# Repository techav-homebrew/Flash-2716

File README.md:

# Flash-2716

This is an adapter for using a 39F010 similar PLCC-32 flash in place of a 2716 or 2732 EPROM. Includes footprint & jumper to use original EPROM as well as an additional disconnected footprint for storing the original EPROM out of circuit.

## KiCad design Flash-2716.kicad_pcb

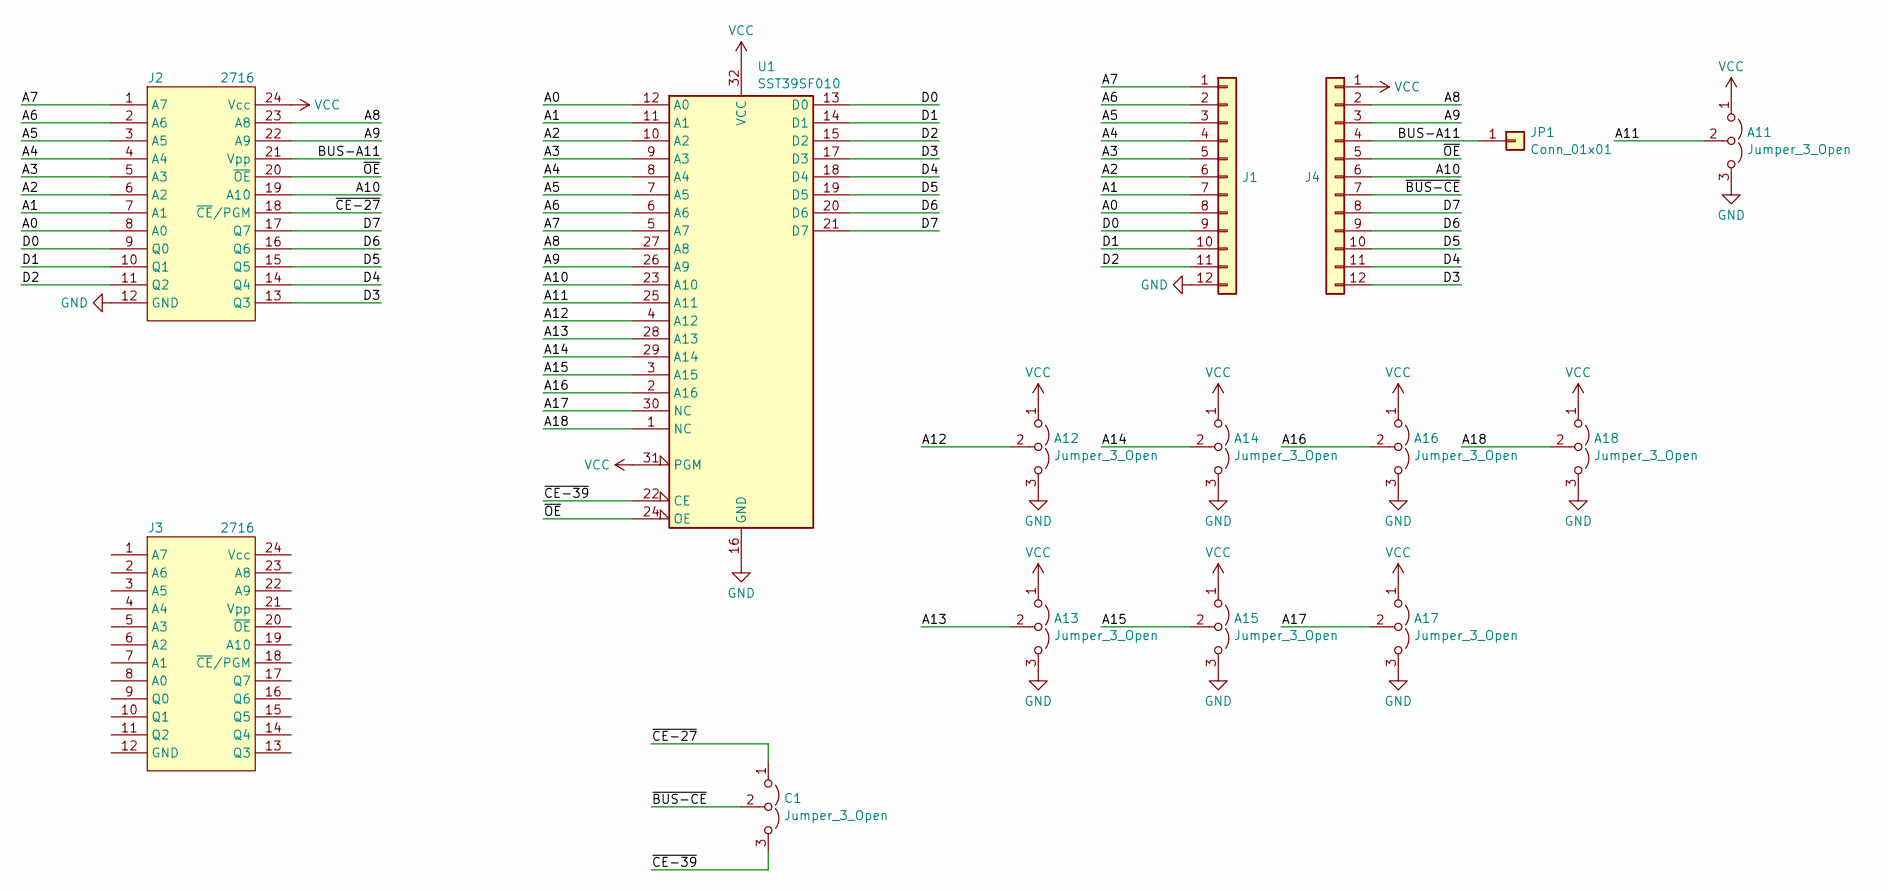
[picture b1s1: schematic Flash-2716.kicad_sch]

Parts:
A11, A12, A13, A14, A15, A16, A17, A18: Jumper_3_Open; PinHeader_1x03_P2.54mm_Vertical
C1: Jumper_3_Open; PinHeader_1x03_P2.54mm_Vertical
J1, J4: Conn_01x12; PinHeader_1x12_P2.54mm_Vertical
J2, J3: 2716; DIP-24_W15.24mm_Socket
JP1: Conn_01x01; PinHeader_1x01_P2.54mm_Vertical
U1: SST39SF010; PLCC-32_THT-Socket

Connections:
/A0: J1.8, J2.8 (A0), U1.12 (A0)
/A1: J1.7, J2.7 (A1), U1.11 (A1)
/A2: J1.6, J2.6 (A2), U1.10 (A2)
/A3: J1.5, J2.5 (A3), U1.9 (A3)
/A4: J1.4, J2.4 (A4), U1.8 (A4)
/A5: J1.3, J2.3 (A5), U1.7 (A5)
/A6: J1.2, J2.2 (A6), U1.6 (A6)
/A7: J1.1, J2.1 (A7), U1.5 (A7)
/A8: J2.23 (A8), J4.2, U1.27 (A8)
/A9: J2.22 (A9), J4.3, U1.26 (A9)
/A10: J2.19 (A10), J4.6, U1.23 (A10)
/A11: A11.2 (C), U1.25 (A11)
/A12: A12.2 (C), U1.4 (A12)
/A13: A13.2 (C), U1.28 (A13)
/A14: A14.2 (C), U1.29 (A14)
/A15: A15.2 (C), U1.3 (A15)
/A16: A16.2 (C), U1.2 (A16)
/A17: A17.2 (C), U1.30 (NC)
/A18: A18.2 (C), U1.1 (NC)
/BUS-A11: J2.21 (Vpp), J4.4, JP1.1
/D0: J1.9, J2.9 (Q0), U1.13 (D0)
/D1: J1.10, J2.10 (Q1), U1.14 (D1)
/D2: J1.11, J2.11 (Q2), U1.15 (D2)
/D3: J2.13 (Q3), J4.12, U1.17 (D3)
/D4: J2.14 (Q4), J4.11, U1.18 (D4)
/D5: J2.15 (Q5), J4.10, U1.19 (D5)
/D6: J2.16 (Q6), J4.9, U1.20 (D6)
/D7: J2.17 (Q7), J4.8, U1.21 (D7)
/~BUS-CE: C1.2 (C), J4.7
/~CE-27: C1.1 (A), J2.18 (~CE/PGM)
/~CE-39: C1.3 (B), U1.22 (CE)
/~OE: J2.20 (~OE), J4.5, U1.24 (OE)
GND: A11.3 (B), A12.3 (B), A13.3 (B), A14.3 (B), A15.3 (B), A16.3 (B), A17.3 (B), A18.3 (B), J1.12, J2.12 (GND), U1.16 (GND)
VCC: A11.1 (A), A12.1 (A), A13.1 (A), A14.1 (A), A15.1 (A), A16.1 (A), A17.1 (A), A18.1 (A), J2.24 (Vcc), J4.1, U1.31 (PGM), U1.32 (VCC)

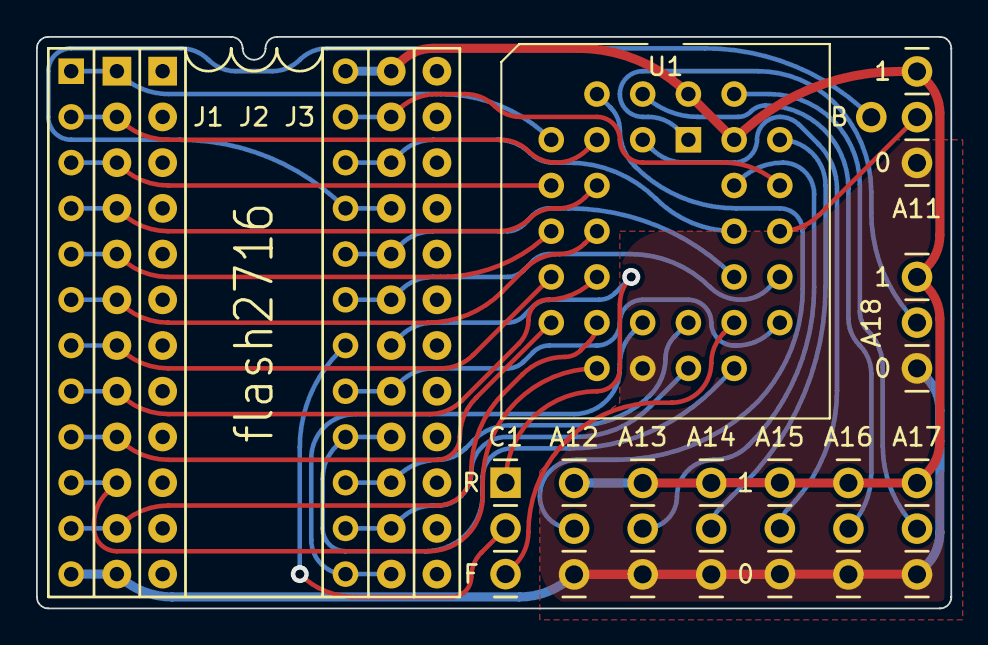
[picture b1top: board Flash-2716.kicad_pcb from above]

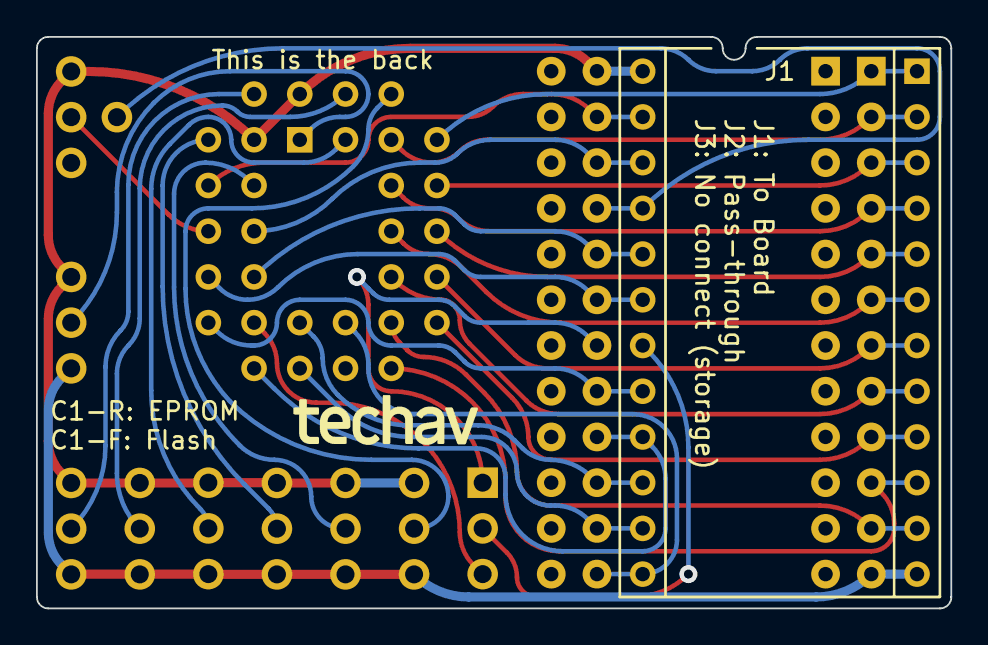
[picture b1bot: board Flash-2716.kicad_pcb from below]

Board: 2 copper layers, 50.8 x 31.8 mm, 15 parts (2 on the bottom side), 34 nets.

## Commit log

2024-11-26 Add 2716 socket & storage
2024-11-27 Cleanup & plot gerbers
2024-11-27 start readme
